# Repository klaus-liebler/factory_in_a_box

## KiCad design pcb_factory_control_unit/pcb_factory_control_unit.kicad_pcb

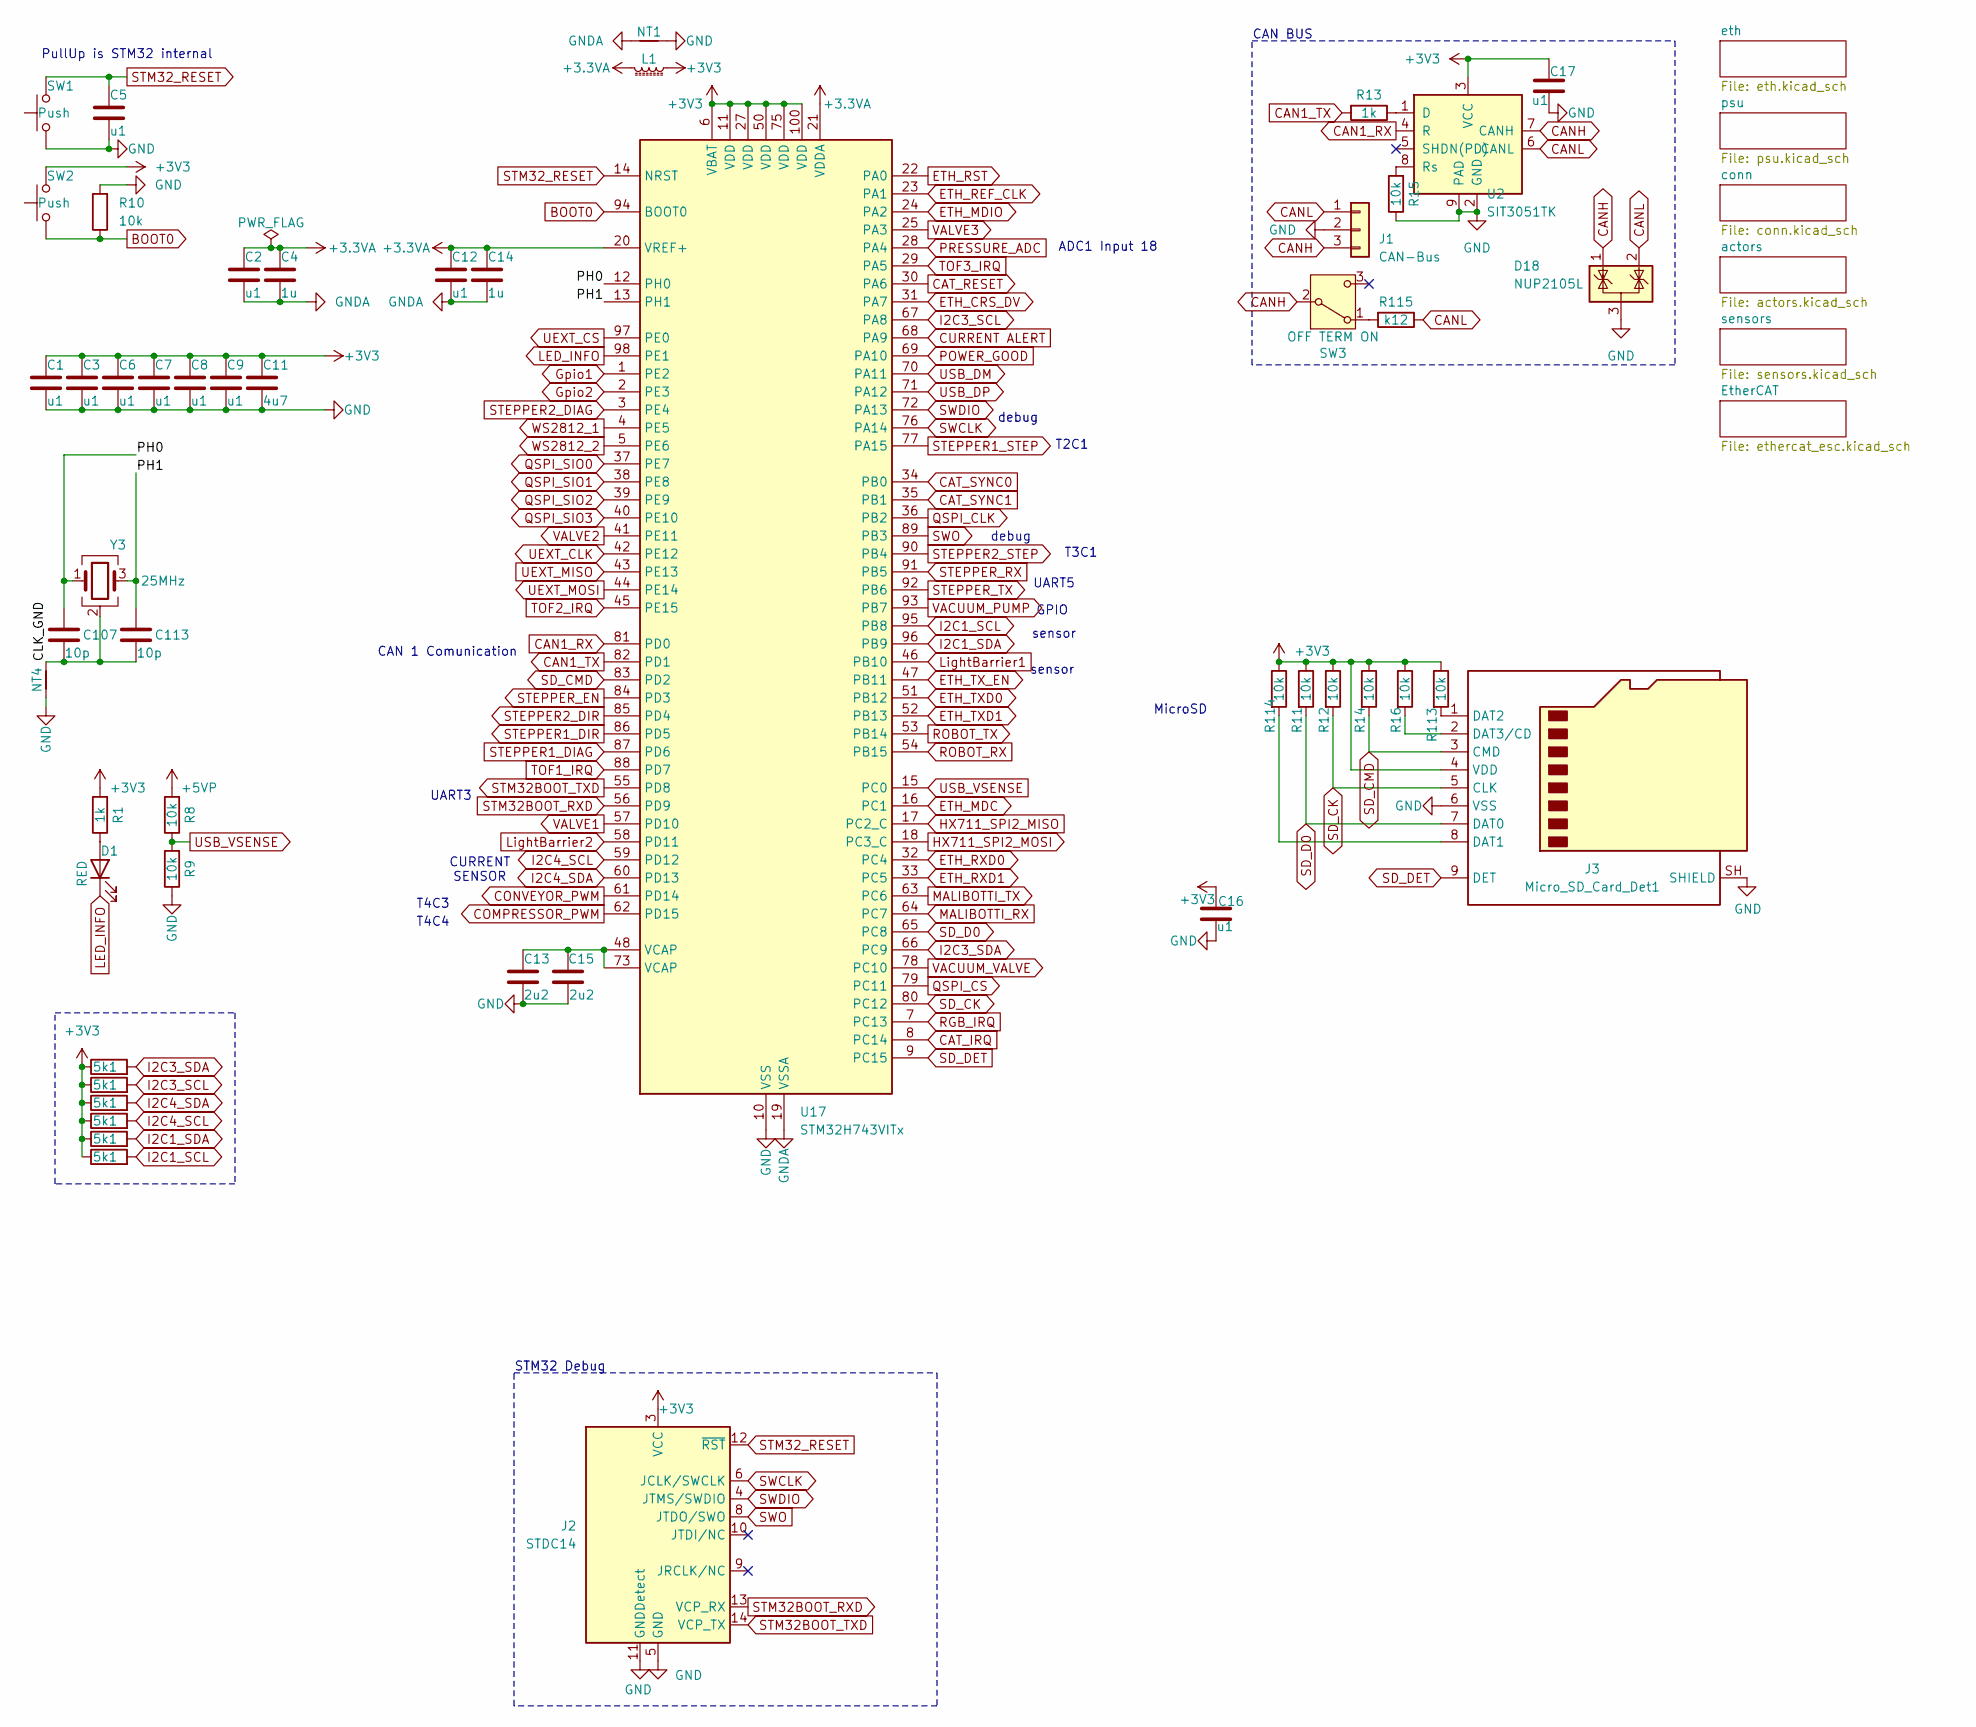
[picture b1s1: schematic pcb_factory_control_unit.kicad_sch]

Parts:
C1, C2, C3, C5, C6, C7, C8, C9, C12, C16, C17: u1; C_0402_1005Metric; MPN CL05B104KO5NNNC; LCSC C1525
C4, C14: 1u; C_0402_1005Metric; MPN CL05A105KA5NQNC; LCSC C52923
C11: 4u7; C_0402_1005Metric; LCSC C307423
C13, C15: 2u2; C_0402_1005Metric; MPN CL05A225MQ5NSNC; LCSC C12530
C107, C113: 10p; C_0402_1005Metric; MPN CC0402JRNPO9BN100; LCSC C106199
D1: RED; LED_1206_3216Metric_ReverseMount_Hole1.8x2.4mm; MPN P2-1206RTCS2-0.9T-F; LCSC C2827254
D18: NUP2105L; SOT-23; MPN NUP2105LT1G; LCSC C2976509
J1: CAN-Bus; JST_XH_B3B-XH-A_1x03_P2.50mm_Vertical_smaller
J2: STDC14; IDC-Header_2x07_P1.27mm_Vertical_SMD; LCSC C6332251
J3: Micro_SD_Card_Det1; microSD push; MPN TF PUSH; LCSC C381082
L1: 220R@100M; L_0603_1608Metric; MPN BLM18PG221SN1D; LCSC C80165
NT1, NT4: NetTie_2; NetTie-2_SMD_Pad0.5mm
R1, R13: 1k; R_0402_1005Metric; MPN 0402WGF1001TCE; LCSC C11702
R2, R3, R4, R5, R6, R7: 5k1; R_0402_1005Metric; MPN 0402WGF5101TCE; LCSC C25905
R8, R9, R10, R11, R12, R14, R15, R16, R113, R114: 10k; R_0402_1005Metric; MPN 0402WGF1002TCE; LCSC C25744
R115: k12; R_0805_2012Metric; MPN 0805W8F1200T5E; LCSC C17437
SW1, SW2: Push; SW_SPST_TL3342_smaller; LCSC C318884
SW3: OFF TERM ON; SW_SPDT_PCM12; MPN PCM12SMTR; LCSC C221841
U2: SIT3051TK; DFN-8-1EP_3x3mm_P0.65mm_EP1.55x2.4mm; LCSC C601078
U17: STM32H743VITx; LQFP-100_14x14mm_P0.5mm
Y3: 25MHz; Crystal_SMD_2016-4Pin_2.0x1.6mm; LCSC C19711739

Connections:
+3.3VA: C2.1, C4.1, C12.1, C14.1, L1.2, U17.20 (VREF+), U17.21 (VDDA)
+3V3: C1.1, C3.1, C6.1, C7.1, C8.1, C9.1, C11.1, C16.2, C17.1, J2.3 (VCC), J3.4 (VDD), L1.1, R1.2, R2.1, R3.1, R4.1, R5.1, R6.1, R7.1, R11.1, R12.1, R14.1, R16.1, R113.1, R114.1, SW2.2, U2.3 (VCC), U17.6 (VBAT), U17.11 (VDD), U17.27 (VDD), U17.50 (VDD), U17.75 (VDD), U17.100 (VDD); also elsewhere on the board
+5VP: R8.2; also elsewhere on the board
/CLK_GND: C107.2, C113.2, NT4.2, Y3.2 (G), Y3.4 (G)
/PH0: C107.1, U17.12 (PH0), Y3.1
/PH1: C113.1, U17.13 (PH1), Y3.3
BOOT0: R10.1, SW2.1, U17.94 (BOOT0)
CAN1_RX: U2.4 (R), U17.81 (PD0)
CAN1_TX: R13.2, U17.82 (PD1)
CANH: D18.1 (K), J1.3, SW3.2 (B), U2.7 (CANH)
CANL: D18.2 (K), J1.1, R115.1, U2.6 (CANL)
CAT_IRQ: U17.8 (PC14); also elsewhere on the board
CAT_RESET: U17.30 (PA6); also elsewhere on the board
CAT_SYNC0: U17.34 (PB0); also elsewhere on the board
CAT_SYNC1: U17.35 (PB1); also elsewhere on the board
COMPRESSOR_PWM: U17.62 (PD15); also elsewhere on the board
CONVEYOR_PWM: U17.61 (PD14); also elsewhere on the board
CURRENT ALERT: U17.68 (PA9); also elsewhere on the board
ETH_CRS_DV: U17.31 (PA7); also elsewhere on the board
ETH_MDC: U17.16 (PC1); also elsewhere on the board
ETH_MDIO: U17.24 (PA2); also elsewhere on the board
ETH_REF_CLK: U17.23 (PA1); also elsewhere on the board
ETH_RST: U17.22 (PA0); also elsewhere on the board
ETH_RXD0: U17.32 (PC4); also elsewhere on the board
ETH_RXD1: U17.33 (PC5); also elsewhere on the board
ETH_TXD0: U17.51 (PB12); also elsewhere on the board
ETH_TXD1: U17.52 (PB13); also elsewhere on the board
ETH_TX_EN: U17.47 (PB11); also elsewhere on the board
GND: C1.2, C3.2, C5.2, C6.2, C7.2, C8.2, C9.2, C11.2, C13.2, C15.2, C16.1, C17.2, D18.3 (A), J1.2, J2.5 (GND), J2.7 (GND), J2.11 (GNDDetect), J3.6 (VSS), J3.SH (SHIELD), NT1.2, NT4.1, R9.1, R10.2, R15.1, SW1.1, U2.2 (GND), U2.9 (PAD), U17.10 (VSS), U17.26 (VSS), U17.49 (VSS), U17.74 (VSS), U17.99 (VSS); also elsewhere on the board
GNDA: C2.2, C4.2, C12.2, C14.2, NT1.1, U17.19 (VSSA)
Gpio1: U17.1 (PE2); also elsewhere on the board
Gpio2: U17.2 (PE3); also elsewhere on the board
HX711_SPI2_MISO: U17.17 (PC2_C); also elsewhere on the board
HX711_SPI2_MOSI: U17.18 (PC3_C); also elsewhere on the board
I2C1_SCL: R7.2, U17.95 (PB8); also elsewhere on the board
I2C1_SDA: R6.2, U17.96 (PB9); also elsewhere on the board
I2C3_SCL: R3.2, U17.67 (PA8); also elsewhere on the board
I2C3_SDA: R2.2, U17.66 (PC9); also elsewhere on the board
I2C4_SCL: R5.2, U17.59 (PD12); also elsewhere on the board
I2C4_SDA: R4.2, U17.60 (PD13); also elsewhere on the board
LED_INFO: D1.1 (K), U17.98 (PE1)
LightBarrier1: U17.46 (PB10); also elsewhere on the board
LightBarrier2: U17.58 (PD11); also elsewhere on the board
MALIBOTTI_RX: U17.64 (PC7); also elsewhere on the board
MALIBOTTI_TX: U17.63 (PC6); also elsewhere on the board
unnamed: C13.1, C15.1, U17.48 (VCAP), U17.73 (VCAP)
unnamed: D1.2 (A), R1.1
unnamed: J3.8 (DAT1), R114.2
unnamed: J3.1 (DAT2), R113.2
unnamed: J3.2 (DAT3/CD), R16.2
unnamed: R115.2, SW3.1 (A)
unnamed: R13.1, U2.1 (D)
unnamed: R15.2, U2.8 (Rs)
POWER_GOOD: U17.69 (PA10); also elsewhere on the board
PRESSURE_ADC: U17.28 (PA4); also elsewhere on the board
QSPI_CLK: U17.36 (PB2); also elsewhere on the board
QSPI_CS: U17.79 (PC11); also elsewhere on the board
QSPI_SIO0: U17.37 (PE7); also elsewhere on the board
QSPI_SIO1: U17.38 (PE8); also elsewhere on the board
QSPI_SIO2: U17.39 (PE9); also elsewhere on the board
QSPI_SIO3: U17.40 (PE10); also elsewhere on the board
RGB_IRQ: U17.7 (PC13); also elsewhere on the board
ROBOT_RX: U17.54 (PB15); also elsewhere on the board
ROBOT_TX: U17.53 (PB14); also elsewhere on the board
SD_CK: J3.5 (CLK), R12.2, U17.80 (PC12)
SD_CMD: J3.3 (CMD), R14.2, U17.83 (PD2)
SD_D0: J3.7 (DAT0), R11.2, U17.65 (PC8)
SD_DET: J3.9 (DET), U17.9 (PC15)
STEPPER1_DIAG: U17.87 (PD6); also elsewhere on the board
STEPPER1_DIR: U17.86 (PD5); also elsewhere on the board
STEPPER1_STEP: U17.77 (PA15); also elsewhere on the board
STEPPER2_DIAG: U17.3 (PE4); also elsewhere on the board
STEPPER2_DIR: U17.85 (PD4); also elsewhere on the board
STEPPER2_STEP: U17.90 (PB4); also elsewhere on the board
STEPPER_EN: U17.84 (PD3); also elsewhere on the board
STEPPER_RX: U17.91 (PB5); also elsewhere on the board
STEPPER_TX: U17.92 (PB6); also elsewhere on the board
STM32BOOT_RXD: J2.13 (VCP_RX), U17.56 (PD9)
STM32BOOT_TXD: J2.14 (VCP_TX), U17.55 (PD8)
STM32_RESET: C5.1, J2.12 (~RST), SW1.2, U17.14 (NRST)
SWCLK: J2.6 (JCLK/SWCLK), U17.76 (PA14)
SWDIO: J2.4 (JTMS/SWDIO), U17.72 (PA13)
SWO: J2.8 (JTDO/SWO), U17.89 (PB3)
TOF1_IRQ: U17.88 (PD7); also elsewhere on the board
TOF2_IRQ: U17.45 (PE15); also elsewhere on the board
TOF3_IRQ: U17.29 (PA5); also elsewhere on the board
UEXT_CLK: U17.42 (PE12); also elsewhere on the board
UEXT_CS: U17.97 (PE0); also elsewhere on the board
UEXT_MISO: U17.43 (PE13); also elsewhere on the board
UEXT_MOSI: U17.44 (PE14); also elsewhere on the board
USB_DM: U17.70 (PA11); also elsewhere on the board
USB_DP: U17.71 (PA12); also elsewhere on the board
USB_VSENSE: R8.1, R9.2, U17.15 (PC0)
VACUUM_PUMP: U17.93 (PB7); also elsewhere on the board
VACUUM_VALVE: U17.78 (PC10); also elsewhere on the board
VALVE1: U17.57 (PD10); also elsewhere on the board
VALVE2: U17.41 (PE11); also elsewhere on the board
VALVE3: U17.25 (PA3); also elsewhere on the board
WS2812_1: U17.4 (PE5); also elsewhere on the board
WS2812_2: U17.5 (PE6); also elsewhere on the board

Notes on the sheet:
T4C3
CAN 1 Comunication
debug
MicroSD
T2C1
UART5
CAN BUS
UART3
sensor
ADC1 Input 18
STM32 Debug
CURRENT SENSOR
PullUp is STM32 internal
T4C4
T3C1
GPIO

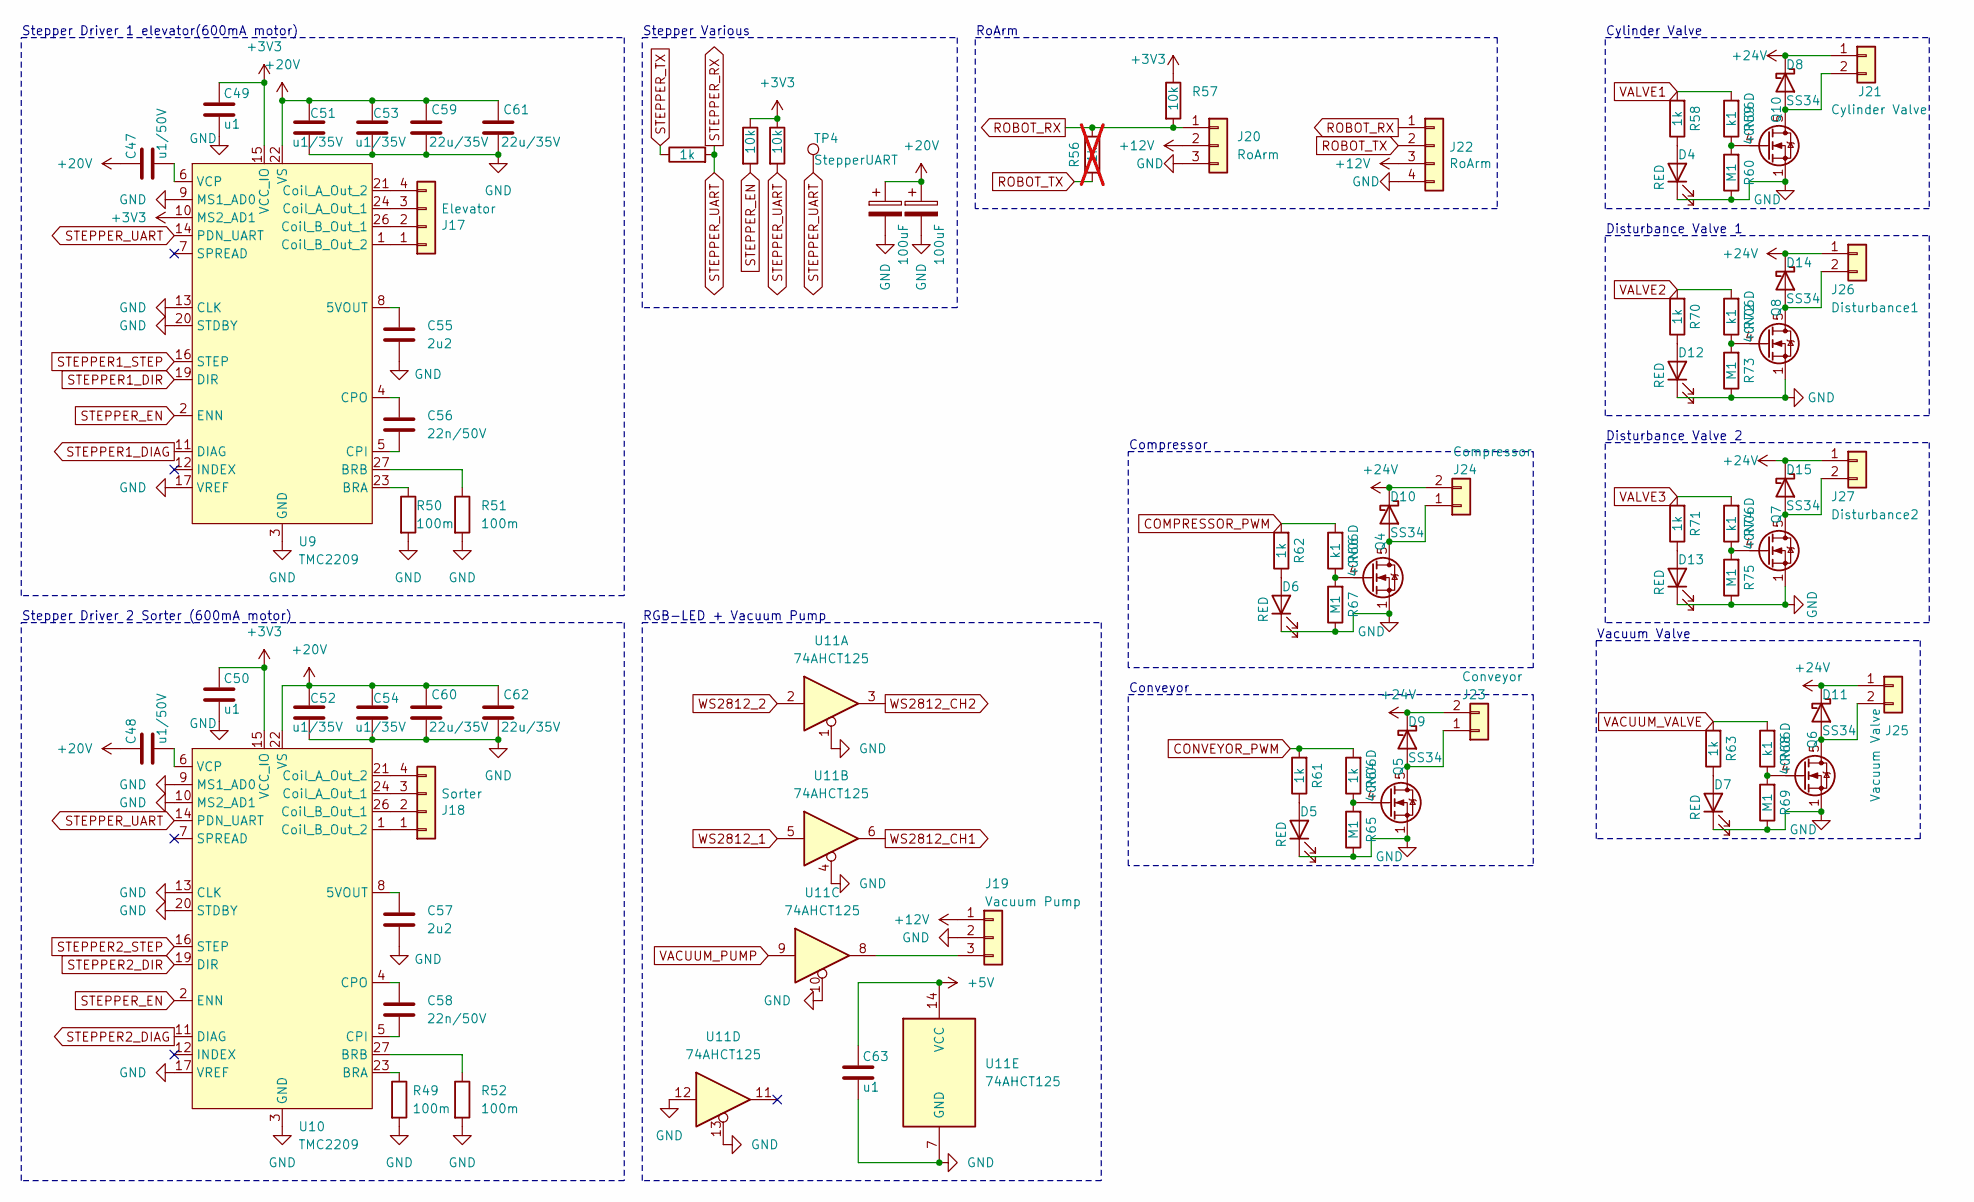
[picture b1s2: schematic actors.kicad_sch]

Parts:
C47, C48: u1/50V; C_0805_2012Metric; MPN CC0805KRX7R9BB104; LCSC C49678
C49, C50, C63: u1; C_0402_1005Metric; MPN CL05B104KO5NNNC; LCSC C1525
C51, C52, C53, C54: u1/35V; C_0805_2012Metric; MPN CC0805KRX7R9BB104; LCSC C49678
C55, C57: 2u2; C_0402_1005Metric; MPN CL05A225MQ5NSNC; LCSC C12530
C56, C58: 22n/50V; C_0402_1005Metric; MPN 0402B223K500NT; LCSC C1532
C59, C60, C61, C62: 22u/35V; C_0805_2012Metric; MPN CGA0805X5R226M350MT; LCSC C6119901
C64, C65: 100uF; CP_Elec_6.3x7.7; MPN RVT1V101M0607; LCSC C72478
D4, D5, D6, D7, D12, D13: RED; LED_1206_3216Metric_ReverseMount_Hole1.8x2.4mm; MPN P2-1206RTCS2-0.9T-F; LCSC C2827254
D8, D9, D10, D11, D14, D15: SS34; D_SMA; MPN SS34; LCSC C8678
J17: Elevator; JST_XH_B4B-XH-A_1x04_P2.50mm_Vertical_smaller; MPN XH-4AW
J18: Sorter; JST_XH_B4B-XH-A_1x04_P2.50mm_Vertical_smaller; MPN XH-4AW
J19: Vacuum Pump; JST_XH_B3B-XH-A_1x03_P2.50mm_Vertical_smaller
J20: RoArm; Molex_SPOX_5267-03A_1x03_P2.50mm_Vertical; MPN 5267-03A / 22035035
J21: Cylinder Valve; JST_XH_B2B-XH-A_1x02_P2.50mm_Vertical
J22: RoArm; JST_XH_B4B-XH-A_1x04_P2.50mm_Vertical_smaller; MPN XH-4AW
J23: Conveyor; PhoenixContact_MC_1,5_2-G-3.5_1x02_P3.50mm_Horizontal_small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
J24: Compressor; PhoenixContact_MC_1,5_2-G-3.5_1x02_P3.50mm_Horizontal_small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
J25: Vacuum Valve; JST_XH_B2B-XH-A_1x02_P2.50mm_Vertical
J26: Disturbance1; JST_XH_B2B-XH-A_1x02_P2.50mm_Vertical
J27: Disturbance2; JST_XH_B2B-XH-A_1x02_P2.50mm_Vertical
Q4, Q5, Q6, Q7, Q8, Q10: 40N06D; VSON-8_3.3x3.3mm_P0.65mm_NexFET; MPN 40N06D; LCSC C7543836
R49, R50, R51, R52: 100m; R_1206_3216Metric; MPN FRM121WFR100TM; LCSC C7467250
R53, R58, R61, R62, R63, R64, R70, R71: 1k; R_0402_1005Metric; MPN 0402WGF1001TCE; LCSC C11702
R54, R55, R57: 10k; R_0402_1005Metric; MPN 0402WGF1002TCE; LCSC C25744
R56: 1k; R_0805_2012Metric_Pad1.20x1.40mm_HandSolder; not fitted
R59, R66, R68, R72, R74: k1; R_0402_1005Metric; MPN 0402WGF1000TCE; LCSC C25076
R60, R65, R67, R69, R73, R75: M1; R_0402_1005Metric; MPN 0402WGF1003TCE; LCSC C25741
TP4: StepperUART; TestPoint_THTPad_D1.0mm_Drill0.5mm
U9, U10: TMC2209; QFN-28-1EP_5x5mm_P0.5mm_EP3.75x3.75mm_ThermalVias; MPN TMC2209-LA-T; LCSC C2150710
U11: 74AHCT125; SOIC-14_3.9x8.7mm_P1.27mm; LCSC C155176

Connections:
+3V3: C49.1, C50.1, R54.1, R55.1, R57.1, U9.10 (MS2_AD1), U9.15 (VCC_IO), U10.15 (VCC_IO); also elsewhere on the board
+5V: C63.1, U11.14 (VCC); also elsewhere on the board
+12V: J19.1, J20.2, J22.3; also elsewhere on the board
+20V: C47.1, C48.1, C51.1, C52.1, C53.1, C54.1, C59.2, C60.2, C61.2, C62.2, C64.1, C65.1, U9.22 (VS), U9.28 (VS), U10.22 (VS), U10.28 (VS); also elsewhere on the board
+24V: D8.1 (K), D9.1 (K), D10.1 (K), D11.1 (K), D14.1 (K), D15.1 (K), J21.1, J23.2, J24.2, J25.1, J26.1, J27.1; also elsewhere on the board
COMPRESSOR_PWM: R62.2, R66.2; also elsewhere on the board
CONVEYOR_PWM: R61.2, R64.2; also elsewhere on the board
GND: C49.2, C50.2, C51.2, C52.2, C53.2, C54.2, C55.2, C57.2, C59.1, C60.1, C61.1, C62.1, C63.2, C64.2, C65.2, D4.1 (K), D5.1 (K), D6.1 (K), D7.1 (K), D12.1 (K), D13.1 (K), J19.2, J20.3, J22.4, Q4.1 (S), Q4.2 (S), Q4.3 (S), Q5.1 (S), Q5.2 (S), Q5.3 (S), Q6.1 (S), Q6.2 (S), Q6.3 (S), Q7.1 (S), Q7.2 (S), Q7.3 (S), Q8.1 (S), Q8.2 (S), Q8.3 (S), Q10.1 (S), Q10.2 (S), Q10.3 (S), R49.2, R50.2, R51.2, R52.2, R60.1, R65.1, R67.1, R69.1, R73.1, R75.1, U9.3 (GND), U9.9 (MS1_AD0), U9.13 (CLK), U9.17 (VREF), U9.18 (GND), U9.20 (STDBY), U9.25 (GND), U9.29 (PAD), U10.3 (GND), U10.9 (MS1_AD0), U10.10 (MS2_AD1), U10.13 (CLK), U10.17 (VREF), U10.18 (GND), U10.20 (STDBY), U10.25 (GND), U10.29 (PAD), U11.1, U11.4, U11.7 (GND), U11.10, U11.12, U11.13; also elsewhere on the board
unnamed: D4.2 (A), R58.1
unnamed: D5.2 (A), R61.1
unnamed: D6.2 (A), R62.1
unnamed: D7.2 (A), R63.1
unnamed: D8.2 (A), J21.2, Q10.5 (D)
unnamed: D9.2 (A), J23.1, Q5.5 (D)
unnamed: D10.2 (A), J24.1, Q4.5 (D)
unnamed: D11.2 (A), J25.2, Q6.5 (D)
unnamed: D12.2 (A), R70.1
unnamed: D13.2 (A), R71.1
unnamed: D14.2 (A), J26.2, Q8.5 (D)
unnamed: D15.2 (A), J27.2, Q7.5 (D)
unnamed: J17.1, U9.1 (Coil_B_Out_2)
unnamed: J17.2, U9.26 (Coil_B_Out_1)
unnamed: J17.3, U9.24 (Coil_A_Out_1)
unnamed: J17.4, U9.21 (Coil_A_Out_2)
unnamed: J18.1, U10.1 (Coil_B_Out_2)
unnamed: J18.2, U10.26 (Coil_B_Out_1)
unnamed: J18.3, U10.24 (Coil_A_Out_1)
unnamed: J18.4, U10.21 (Coil_A_Out_2)
unnamed: J19.3, U11.8
unnamed: Q4.4 (G), R66.1, R67.2
unnamed: Q5.4 (G), R64.1, R65.2
unnamed: Q6.4 (G), R68.1, R69.2
unnamed: Q7.4 (G), R74.1, R75.2
unnamed: Q8.4 (G), R72.1, R73.2
unnamed: Q10.4 (G), R59.1, R60.2
unnamed: C55.1, U9.8 (5VOUT)
unnamed: R50.1, U9.23 (BRA)
unnamed: R51.1, U9.27 (BRB)
unnamed: C56.2, U9.5 (CPI)
unnamed: C56.1, U9.4 (CPO)
unnamed: C47.2, U9.6 (VCP)
unnamed: C57.1, U10.8 (5VOUT)
unnamed: R49.1, U10.23 (BRA)
unnamed: R52.1, U10.27 (BRB)
unnamed: C58.2, U10.5 (CPI)
unnamed: C58.1, U10.4 (CPO)
unnamed: C48.2, U10.6 (VCP)
ROBOT_RX: J20.1, J22.1, R56.2, R57.2; also elsewhere on the board
ROBOT_TX: J22.2, R56.1; also elsewhere on the board
STEPPER1_DIAG: U9.11 (DIAG); also elsewhere on the board
STEPPER1_DIR: U9.19 (DIR); also elsewhere on the board
STEPPER1_STEP: U9.16 (STEP); also elsewhere on the board
STEPPER2_DIAG: U10.11 (DIAG); also elsewhere on the board
STEPPER2_DIR: U10.19 (DIR); also elsewhere on the board
STEPPER2_STEP: U10.16 (STEP); also elsewhere on the board
STEPPER_EN: R54.2, U9.2 (ENN), U10.2 (ENN); also elsewhere on the board
STEPPER_RX: R53.2, R55.2, TP4.1 (1_1), U9.14 (PDN_UART), U10.14 (PDN_UART); also elsewhere on the board
STEPPER_TX: R53.1; also elsewhere on the board
VACUUM_PUMP: U11.9; also elsewhere on the board
VACUUM_VALVE: R63.2, R68.2; also elsewhere on the board
VALVE1: R58.2, R59.2; also elsewhere on the board
VALVE2: R70.2, R72.2; also elsewhere on the board
VALVE3: R71.2, R74.2; also elsewhere on the board
WS2812_1: U11.5; also elsewhere on the board
WS2812_2: U11.2; also elsewhere on the board
WS2812_CH1: U11.6; also elsewhere on the board
WS2812_CH2: U11.3; also elsewhere on the board

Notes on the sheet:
RoArm
Disturbance Valve 1
Vacuum Valve
Compressor
Stepper Driver 2 Sorter (600mA motor)
Disturbance Valve 2
Stepper Driver 1 elevator(600mA motor)
Conveyor
RGB-LED + Vacuum Pump
Stepper Various
Cylinder Valve

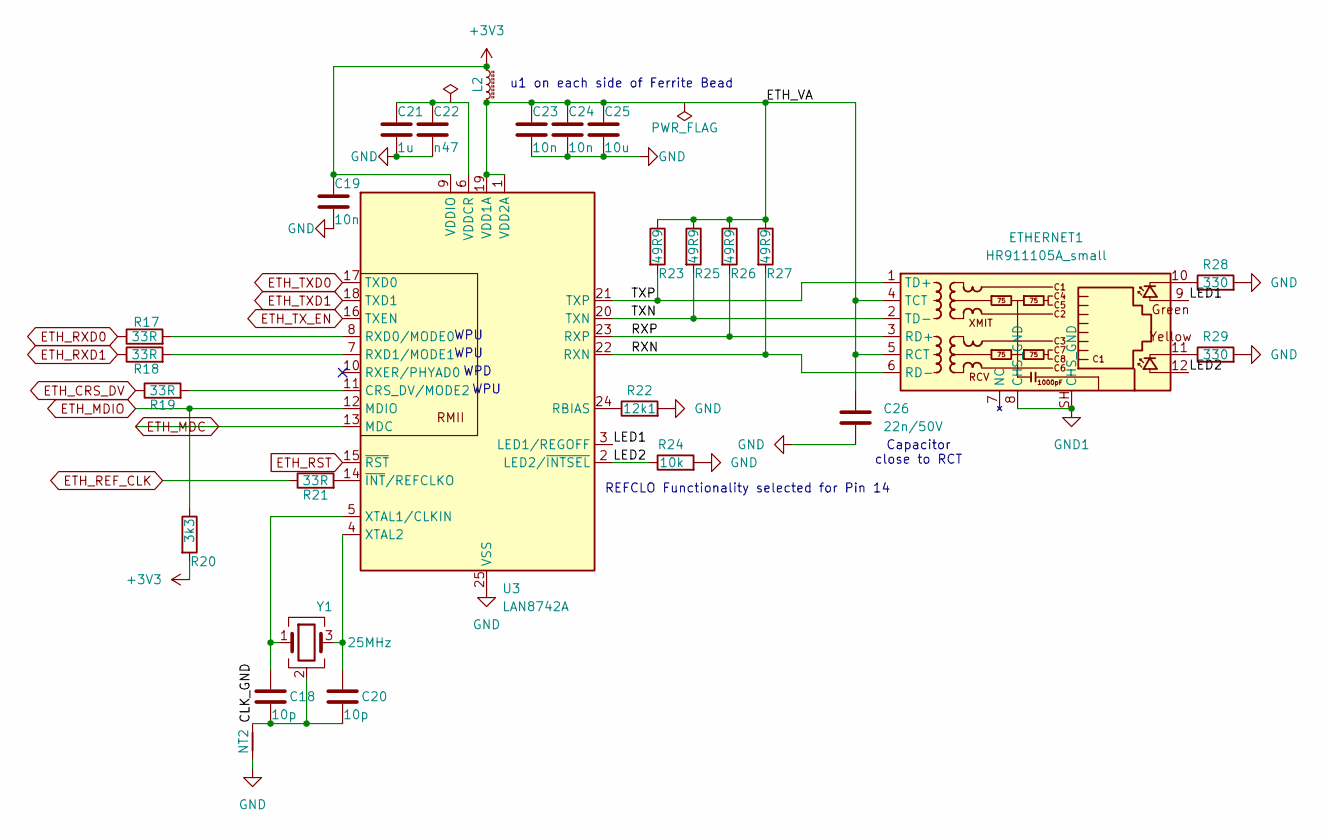
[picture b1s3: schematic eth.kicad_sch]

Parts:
C18, C20: 10p; C_0402_1005Metric; MPN CC0402JRNPO9BN100; LCSC C106199
C19, C23, C24: 10n; C_0402_1005Metric; MPN FCC0402B103K500AT; LCSC C5137480
C21: 1u; C_0402_1005Metric; MPN CL05A105KA5NQNC; LCSC C52923
C22: n47; C_0402_1005Metric; MPN GRM1555C1H471JA01D; LCSC C76971
C25: 10u; C_0805_2012Metric; MPN CGA0805X5R106K500MT; LCSC C6119889
C26: 22n/50V; C_0402_1005Metric; MPN 0402B223K500NT; LCSC C1532
ETHERNET1: HR911105A_small; RJ45_HANRUN_HR911105A; LCSC C12074
L2: 220R@100M; L_0603_1608Metric; MPN BLM18PG221SN1D; LCSC C80165
NT2: NetTie_2; NetTie-2_SMD_Pad0.5mm
R17, R18, R19, R21: 33R; R_0402_1005Metric; LCSC C25105
R20: 3k3; R_0402_1005Metric; MPN 0402WGF3301TCE; LCSC C25890
R22: 12k1; R_0402_1005Metric; LCSC C25852
R23, R25, R26, R27: 49R9; R_0402_1005Metric; LCSC C25120
R24: 10k; R_0402_1005Metric; MPN 0402WGF1002TCE; LCSC C25744
R28, R29: 330; R_0402_1005Metric; MPN 0402WGF3300TCE; LCSC C25104
U3: LAN8742A; VQFN-24-1EP_4x4mm_P0.5mm_EP2.5x2.5mm_ThermalVias; LCSC C621425
Y1: 25MHz; Crystal_SMD_2016-4Pin_2.0x1.6mm; LCSC C19711739

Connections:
+3V3: C19.1, L2.1, R20.2, U3.9 (VDDIO); also elsewhere on the board
/eth/CLK_GND: C18.2, C20.2, NT2.2, Y1.2 (G), Y1.4 (G)
/eth/ETH_VA: C23.1, C24.1, C25.1, C26.1, ETHERNET1.4 (TCT), ETHERNET1.5 (RCT), L2.2, R23.1, R25.1, R26.1, R27.1, U3.1 (VDD2A), U3.19 (VDD1A)
/eth/LED1: ETHERNET1.9, U3.3 (LED1/REGOFF)
/eth/LED2: ETHERNET1.12, R24.1, U3.2 (LED2/~INTSEL)
/eth/RXN: ETHERNET1.6 (RD-), R27.2, U3.22 (RXN)
/eth/RXP: ETHERNET1.3 (RD+), R26.2, U3.23 (RXP)
/eth/TXN: ETHERNET1.2 (TD-), R25.2, U3.20 (TXN)
/eth/TXP: ETHERNET1.1 (TD+), R23.2, U3.21 (TXP)
ETH_CRS_DV: R19.1; also elsewhere on the board
ETH_MDC: U3.13 (MDC); also elsewhere on the board
ETH_MDIO: R20.1, U3.12 (MDIO); also elsewhere on the board
ETH_REF_CLK: R21.1; also elsewhere on the board
ETH_RST: U3.15 (~RST); also elsewhere on the board
ETH_RXD0: R17.1; also elsewhere on the board
ETH_RXD1: R18.1; also elsewhere on the board
ETH_TXD0: U3.17 (TXD0); also elsewhere on the board
ETH_TXD1: U3.18 (TXD1); also elsewhere on the board
ETH_TX_EN: U3.16 (TXEN); also elsewhere on the board
GND: C19.2, C21.2, C22.2, C23.2, C24.2, C25.2, C26.2, NT2.1, R22.2, R24.2, R28.2, R29.2, U3.25 (VSS); also elsewhere on the board
GND1: ETHERNET1.8 (CHS_GND), ETHERNET1.SH (CHS_GND); also elsewhere on the board
unnamed: ETHERNET1.10, R28.1
unnamed: ETHERNET1.11, R29.1
unnamed: R19.2, U3.11 (CRS_DV/MODE2)
unnamed: R22.1, U3.24 (RBIAS)
unnamed: R17.2, U3.8 (RXD0/MODE0)
unnamed: R18.2, U3.7 (RXD1/MODE1)
unnamed: C21.1, C22.1, U3.6 (VDDCR)
unnamed: C18.1, U3.5 (XTAL1/CLKIN), Y1.1
unnamed: C20.1, U3.4 (XTAL2), Y1.3
unnamed: R21.2, U3.14 (~INT/REFCLKO)

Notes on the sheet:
Capacitor close to RCT
u1 on each side of Ferrite Bead
WPU
REFCLO Functionality selected for Pin 14
WPD

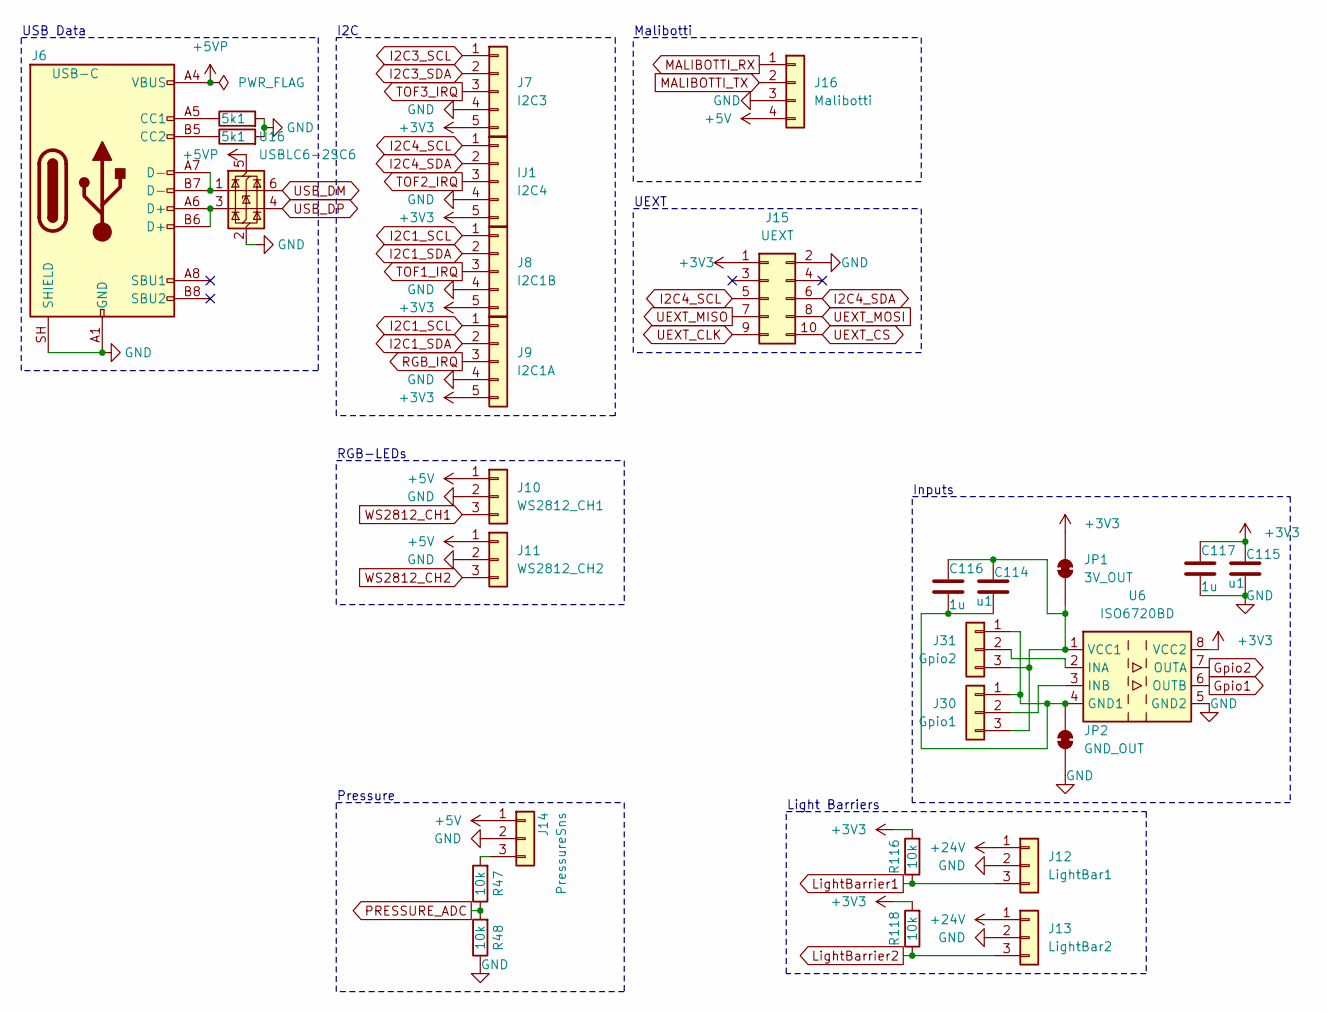
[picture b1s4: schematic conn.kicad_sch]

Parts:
C114, C115: u1; C_0402_1005Metric; MPN CL05B104KO5NNNC; LCSC C1525
C116, C117: 1u; C_0402_1005Metric; MPN CL05A105KA5NQNC; LCSC C52923
IJ1: I2C4; JST_XH_B5B-XH-A_1x05_P2.50mm_Vertical_smaller
J6: USB-C; USB_C_Receptacle_HRO_TYPE-C-31-M-12_smaller; MPN TYPE-C-31-M-12; LCSC C165948
J7: I2C3; JST_XH_B5B-XH-A_1x05_P2.50mm_Vertical_smaller
J8: I2C1B; JST_XH_B5B-XH-A_1x05_P2.50mm_Vertical_smaller
J9: I2C1A; JST_XH_B5B-XH-A_1x05_P2.50mm_Vertical_smaller
J10: WS2812_CH1; JST_XH_B3B-XH-A_1x03_P2.50mm_Vertical_smaller
J11: WS2812_CH2; JST_XH_B3B-XH-A_1x03_P2.50mm_Vertical_smaller
J12: LightBar1; JST_XH_B3B-XH-A_1x03_P2.50mm_Vertical_smaller
J13: LightBar2; JST_XH_B3B-XH-A_1x03_P2.50mm_Vertical_smaller
J14: PressureSns; JST_XH_B3B-XH-A_1x03_P2.50mm_Vertical_smaller
J15: UEXT; IDC-Header_2x05_P2.54mm_Vertical
J16: Malibotti; JST_XH_B4B-XH-A_1x04_P2.50mm_Vertical_smaller
J30: Gpio1; JST_XH_B3B-XH-A_1x03_P2.50mm_Vertical_smaller
J31: Gpio2; JST_XH_B3B-XH-A_1x03_P2.50mm_Vertical_smaller
JP1: 3V_OUT; SolderJumper-2_P1.3mm_Bridged2Bar_RoundedPad1.0x1.5mm
JP2: GND_OUT; SolderJumper-2_P1.3mm_Bridged2Bar_RoundedPad1.0x1.5mm
R45, R46: 5k1; R_0402_1005Metric; MPN 0402WGF5101TCE; LCSC C25905
R47, R48, R116, R118: 10k; R_0402_1005Metric; MPN 0402WGF1002TCE; LCSC C25744
U6: ISO6720BD; SOIC-8_3.9x4.9mm_P1.27mm; LCSC C41409431
U16: USBLC6-2SC6; SOT-23-6; MPN USBLC6-2SC6; LCSC C2687116

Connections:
+3V3: C115.1, C117.1, IJ1.5, J7.5, J8.5, J9.5, J15.1, JP1.2 (B), R116.2, R118.2, U6.8 (VCC2); also elsewhere on the board
+5V: J10.1, J11.1, J14.1, J16.4; also elsewhere on the board
+5VP: J6.A4 (VBUS), J6.A9 (VBUS), J6.B4 (VBUS), J6.B9 (VBUS), U16.5 (VBUS); also elsewhere on the board
+24V: J12.1, J13.1; also elsewhere on the board
GND: C115.2, C117.2, IJ1.4, J6.A1 (GND), J6.A12 (GND), J6.B1 (GND), J6.B12 (GND), J6.SH (SHIELD), J7.4, J8.4, J9.4, J10.2, J11.2, J12.2, J13.2, J14.2, J15.2, J16.3, JP2.1 (A), R45.2, R46.2, R48.1, U6.5 (GND2), U16.2 (GND); also elsewhere on the board
Gpio1: U6.6 (OUTB); also elsewhere on the board
Gpio2: U6.7 (OUTA); also elsewhere on the board
I2C1_SCL: J8.1, J9.1; also elsewhere on the board
I2C1_SDA: J8.2, J9.2; also elsewhere on the board
I2C3_SCL: J7.1; also elsewhere on the board
I2C3_SDA: J7.2; also elsewhere on the board
I2C4_SCL: IJ1.1, J15.5; also elsewhere on the board
I2C4_SDA: IJ1.2, J15.6; also elsewhere on the board
LightBarrier1: J12.3, R116.1; also elsewhere on the board
LightBarrier2: J13.3, R118.1; also elsewhere on the board
MALIBOTTI_RX: J16.1; also elsewhere on the board
MALIBOTTI_TX: J16.2; also elsewhere on the board
unnamed: J6.A5 (CC1), R45.1
unnamed: J6.B5 (CC2), R46.1
unnamed: J6.A6 (D+), J6.B6 (D+), U16.3 (I/O2)
unnamed: J6.A7 (D-), J6.B7 (D-), U16.1 (I/O1)
unnamed: J14.3, R47.2
unnamed: C114.2, C116.2, J30.1, J31.1, JP2.2 (B), U6.4 (GND1)
unnamed: J30.2, U6.3 (INB)
unnamed: C114.1, C116.1, J30.3, J31.3, JP1.1 (A), U6.1 (VCC1)
unnamed: J31.2, U6.2 (INA)
PRESSURE_ADC: R47.1, R48.2; also elsewhere on the board
RGB_IRQ: J9.3; also elsewhere on the board
TOF1_IRQ: J8.3; also elsewhere on the board
TOF2_IRQ: IJ1.3; also elsewhere on the board
TOF3_IRQ: J7.3; also elsewhere on the board
UEXT_CLK: J15.9; also elsewhere on the board
UEXT_CS: J15.10; also elsewhere on the board
UEXT_MISO: J15.7; also elsewhere on the board
UEXT_MOSI: J15.8; also elsewhere on the board
USB_DM: U16.6 (I/O1); also elsewhere on the board
USB_DP: U16.4 (I/O2); also elsewhere on the board
WS2812_CH1: J10.3; also elsewhere on the board
WS2812_CH2: J11.3; also elsewhere on the board

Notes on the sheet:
Pressure
I2C
UEXT
Light Barriers
Inputs
RGB-LEDs
USB Data
Malibotti

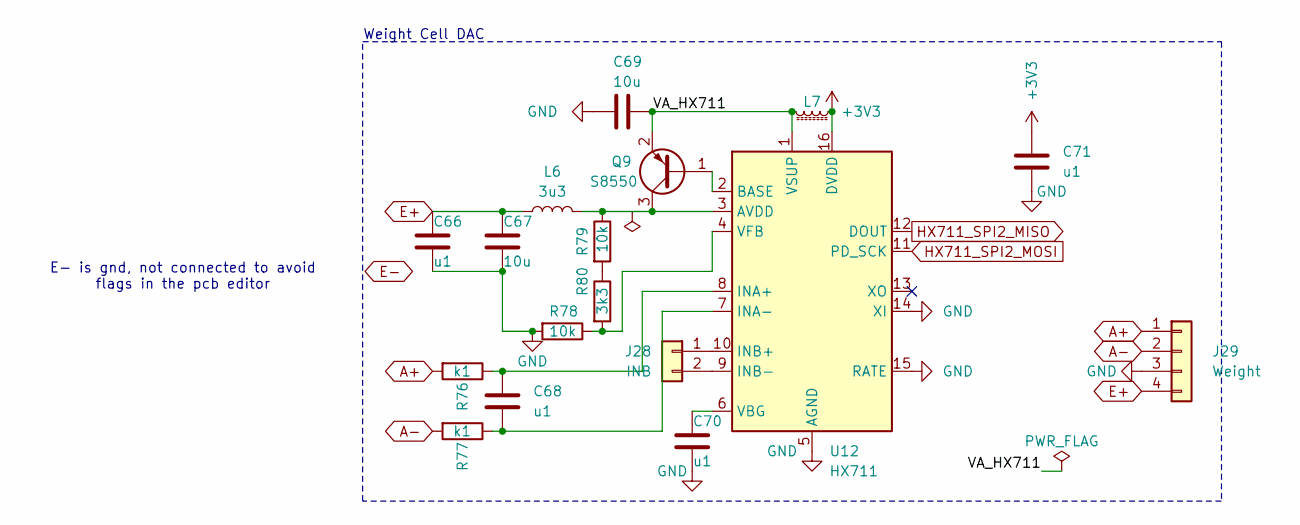
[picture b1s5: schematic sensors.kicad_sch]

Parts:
C66, C68, C70, C71: u1; C_0402_1005Metric; MPN CL05B104KO5NNNC; LCSC C1525
C67, C69: 10u; C_0805_2012Metric; MPN CGA0805X5R106K500MT; LCSC C6119889
J28: INB; JST_XH_B2B-XH-A_1x02_P2.50mm_Vertical
J29: Weight; JST_XH_B4B-XH-A_1x04_P2.50mm_Vertical_smaller
L6: 3u3; L_0805_2012Metric; LCSC C162585
L7: 220R@100M; L_0603_1608Metric; MPN BLM18PG221SN1D; LCSC C80165
Q9: S8550; SOT-23; MPN S8550; LCSC C364313
R76, R77: k1; R_0402_1005Metric; MPN 0402WGF1000TCE; LCSC C25076
R78, R79: 10k; R_0402_1005Metric; MPN 0402WGF1002TCE; LCSC C25744
R80: 3k3; R_0402_1005Metric; MPN 0402WGF3301TCE; LCSC C25890
U12: HX711; SOIC-16_3.9x9.9mm_P1.27mm; LCSC C6705483

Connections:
+3V3: C71.1, L7.1, U12.16 (DVDD); also elsewhere on the board
/sensors/VA_HX711: C69.1, L7.2, Q9.2 (E), U12.1 (VSUP)
A+: J29.1, R76.2
A-: J29.2, R77.2
E+: C66.1, C67.1, J29.4, L6.1
GND: C66.2, C67.2, C69.2, C70.2, C71.2, J29.3, R78.2, U12.5 (AGND), U12.14 (XI), U12.15 (RATE); also elsewhere on the board
HX711_SPI2_MISO: U12.12 (DOUT); also elsewhere on the board
HX711_SPI2_MOSI: U12.11 (PD_SCK); also elsewhere on the board
unnamed: J28.1, U12.10 (INB+)
unnamed: J28.2, U12.9 (INB-)
unnamed: Q9.1 (B), U12.2 (BASE)
unnamed: L6.2, Q9.3 (C), R79.1, U12.3 (AVDD)
unnamed: R79.2, R80.1
unnamed: C68.1, R76.1, U12.8 (INA+)
unnamed: C68.2, R77.1, U12.7 (INA-)
unnamed: C70.1, U12.6 (VBG)
unnamed: R78.1, R80.2, U12.4 (VFB)

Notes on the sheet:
Weight Cell DAC
E- is gnd, not connected to avoid flags in the pcb editor
